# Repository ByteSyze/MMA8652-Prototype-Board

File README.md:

# MMA8652-Prototype-Board
A prototype board for the Freescale MMA8652 accelerometer.
_______________________
In essence, the board follows Freescale's typical application circuit, with an additional power LED because I 
like blinky things. The board only breaks out the chip's SDA and SCL signals.

OSHPark link: https://oshpark.com/shared_projects/eR4QzxW6

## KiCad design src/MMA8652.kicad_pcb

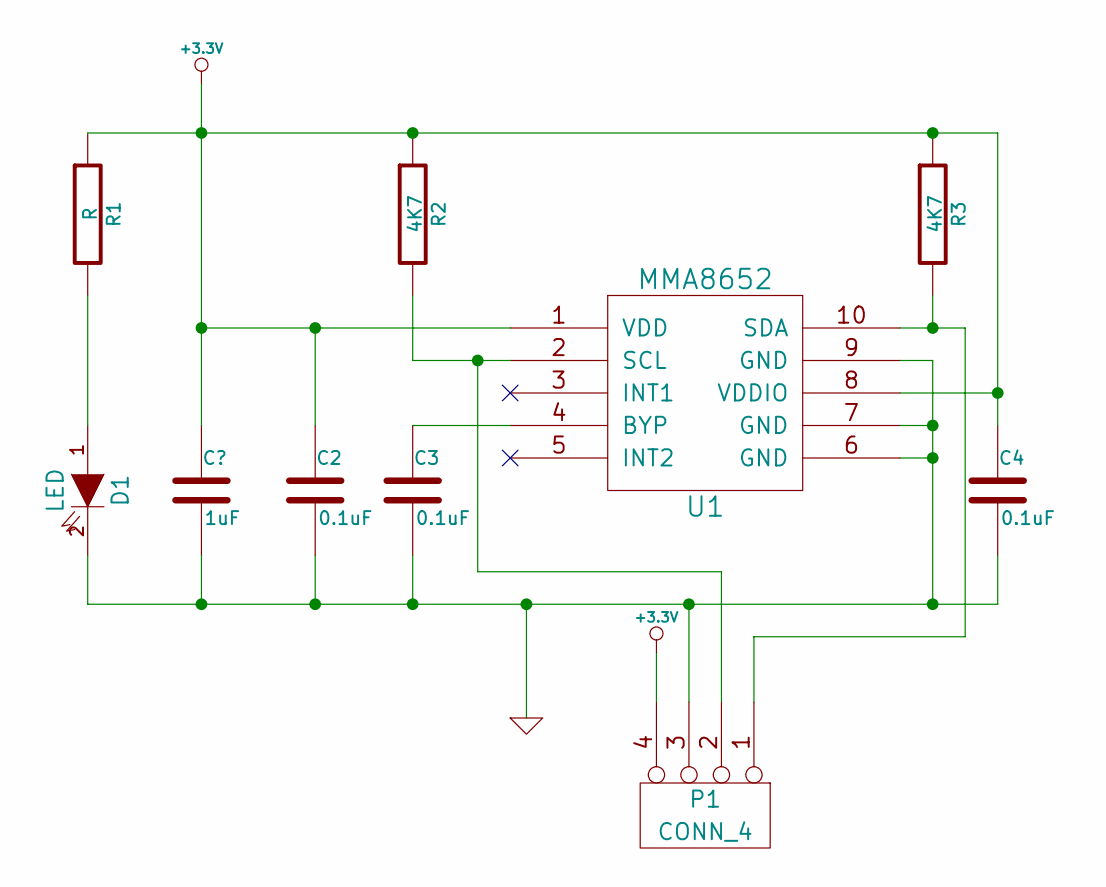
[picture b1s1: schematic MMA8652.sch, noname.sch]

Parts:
C2, C3, C4: 0.1uF
D1: LED
P1: CONN_4
R1: R
R2, R3: 4K7
U1: MMA8652

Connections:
+3.3V: C2.1, C4.1, P1.4, R1.1, R2.1, R3.1, U1.1 (VDD), U1.8 (VDDIO); also elsewhere on the board
GND: C2.2, C3.2, C4.2, D1.2 (K), P1.3, U1.6 (GND), U1.7 (GND), U1.9 (GND); also elsewhere on the board
unnamed: C3.1, U1.4 (BYP)
unnamed: D1.1 (A), R1.2
unnamed: P1.2, R2.2, U1.2 (SCL)
unnamed: P1.1, R3.2, U1.10 (SDA)

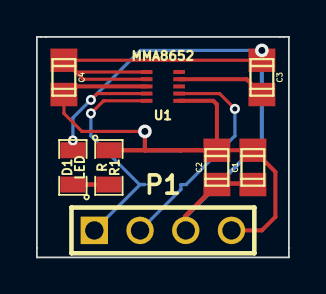
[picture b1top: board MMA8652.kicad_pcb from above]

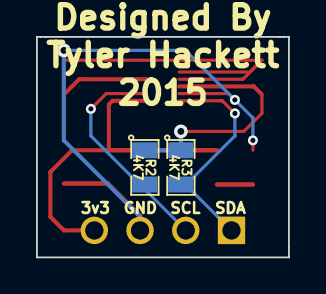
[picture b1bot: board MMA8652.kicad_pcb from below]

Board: 2 copper layers, 14.0 x 12.2 mm, 10 parts (2 on the bottom side), 6 nets.

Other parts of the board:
C1: 1uF; c_0805

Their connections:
+3.3V: C1.1; also elsewhere on the board
GND: C1.2; also elsewhere on the board

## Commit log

2015-01-31 :tada: Added .gitattributes & .gitignore files
2015-01-31 Initial schematic, layout, and gerbers
2015-01-31 Add link to OSHPark upload in README
